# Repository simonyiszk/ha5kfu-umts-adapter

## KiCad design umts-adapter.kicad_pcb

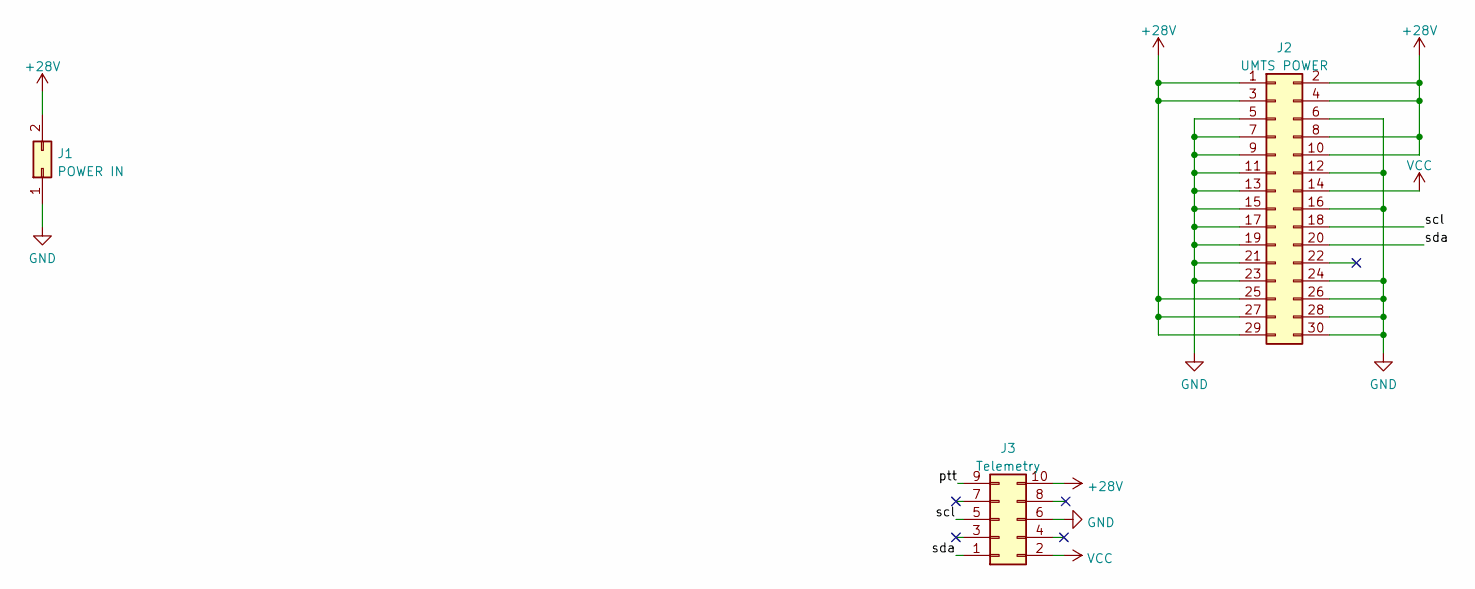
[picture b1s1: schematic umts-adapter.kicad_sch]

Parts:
J1: POWER IN; AMASS_XT60-F_1x02_P7.20mm_Vertical
J2: UMTS POWER; PinHeader_2x15_P1.27mm_Vertical
J3: Telemetry; PinHeader_2x05_P2.54mm_Vertical

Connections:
+28V: J1.2, J2.1, J2.2, J2.3, J2.4, J2.8, J2.10, J2.25, J2.27, J2.29, J3.10
/ptt: J3.9
/scl: J2.18, J3.5
/sda: J2.20, J3.1
GND: J1.1, J2.5, J2.6, J2.7, J2.9, J2.11, J2.12, J2.13, J2.15, J2.16, J2.17, J2.19, J2.21, J2.23, J2.24, J2.26, J2.28, J2.30, J3.6
VCC: J2.14, J3.2

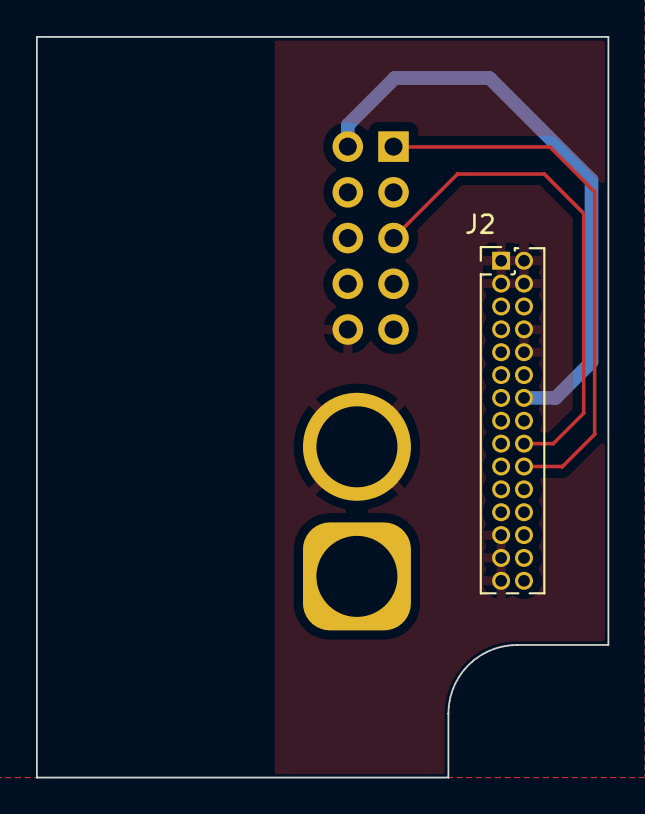
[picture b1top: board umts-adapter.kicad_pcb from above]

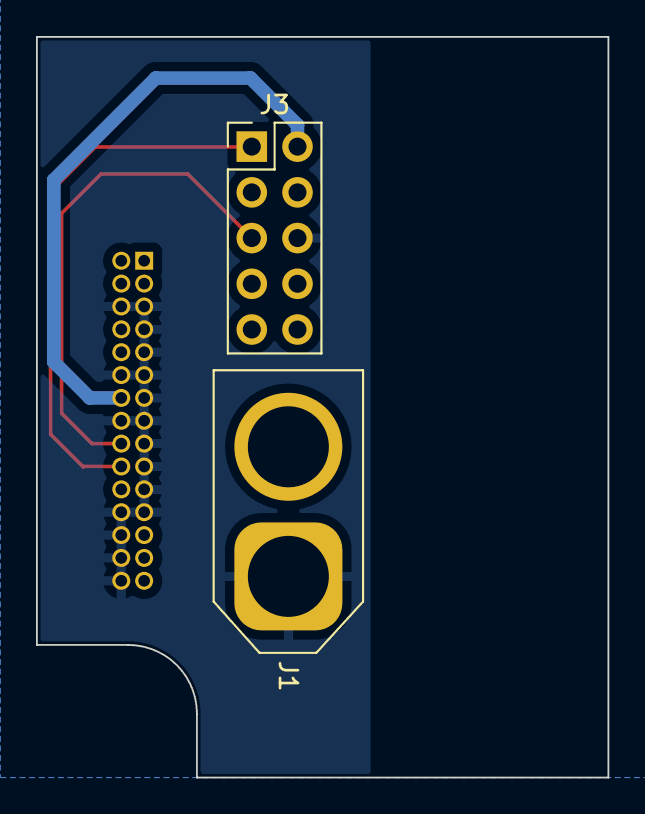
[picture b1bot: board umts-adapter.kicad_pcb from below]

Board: 2 copper layers, 31.8 x 41.1 mm, 3 parts (2 on the bottom side), 5 nets.

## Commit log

2024-06-26 feat: initial revision
2024-06-30 feat: rev1.0, fits without cover. To be redesigned
2024-08-04 !change: updated pcb to fit into built-in holes on the box change: two-stage adjustable regulators
2024-08-11 feat!: removed all extra components to make it just a breakout
2024-12-06 Update to fabricated & tested version
